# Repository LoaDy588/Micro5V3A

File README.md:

# Miniature 5V 3A power module

## BOM
|Reference|Part|Link|
|:--------|----|----|
|C1, C2|10uF, MLCC, 25V, X5R, 0805|[Farnell](https://cz.farnell.com/murata/grm21br61e106ka73l/cap-10-f-25v-10-x5r-0805/dp/1735530)|
|C3|100nF, MLCC, 10V, X7R, 0603|[Farnell](https://cz.farnell.com/multicomp/mcsh18b104k100ct/cap-0-1-f-10v-10-x7r-0603/dp/1856307)|
|C4, C5, C6|22uF, MLCC, 10V, X5R, 1206|[Farnell](https://cz.farnell.com/kemet/c1206c226m8pactu/cap-22-f-10v-20-x5r-1206/dp/1572634)|
|L1|3.3uH|[Farnell](https://cz.farnell.com/kemet/mplch0740l3r3/inductor-3-3uh-20-smd-power/dp/2364595)|
|U1|TPS563209|[Octopart](https://octopart.com/tps563209ddct-texas+instruments-47739788?r=sp&s=za5Sak0sR_WEylk-f30fUg)|
|R1|1K, 1%, 0603|-|
|R2|54K9, 1%, 0603|-|
|R3|10K, 1%, 0603|-|

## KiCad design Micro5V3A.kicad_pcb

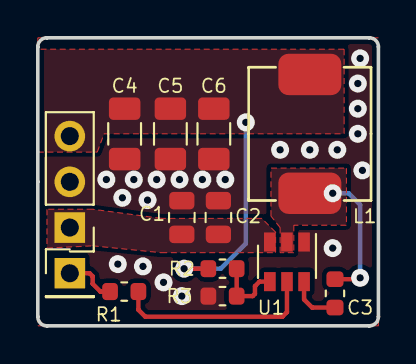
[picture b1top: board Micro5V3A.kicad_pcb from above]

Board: 2 copper layers, 18.9 x 16.0 mm, 13 parts (0 on the bottom side), 8 nets.

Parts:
C1, C2: 10u; C_0805_2012Metric
C3: 100n; C_0603_1608Metric
C4, C5, C6: 22u; C_1206_3216Metric
J1: EnablePin; PinHeader_1x01_P2.54mm_Vertical
J2: Conn_01x03; PinHeader_1x03_P2.54mm_Vertical
L1: 3u3; 7.3x6.7_SMD_INDUCTOR
R1: 1K; R_0603_1608Metric
R2: 54K9; R_0603_1608Metric
R3: 10K; R_0603_1608Metric
U1: TPS563209; SOT-23-6

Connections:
/5V: C4.1, C5.1, C6.1, J2.3, L1.2, R2.1
/ENABLE: J1.1, R1.2
/VIN: C1.1, C2.1, J2.1, U1.3
GND: C1.2, C2.2, C4.2, C5.2, C6.2, J2.2, R3.2, U1.1
unnamed: C3.1, U1.6
unnamed: C3.2, L1.1, U1.2
unnamed: R1.1, U1.5
unnamed: R2.2, R3.1, U1.4

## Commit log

2019-04-03 slight edit
2019-04-03 add rounded corners
2019-04-09 Rev2 - LM7805 compatible pinout
